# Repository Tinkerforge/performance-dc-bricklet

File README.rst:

Performance DC Bricklet
=======================

This repository contains the firmware source code and the hardware design
files. The documentation generator configs can be found at
https://github.com/Tinkerforge/generators

Repository Content
------------------

software/:
 * examples/: Examples for all supported languages
 * build/: Compiled files
 * src/: Source code of firmware
 * Makefile: Makefile to build project

hardware/:
 * Contains KiCad project files and additionally schematics as PDF

datasheets/:
 * Contains datasheets for sensors and complex ICs that are used

Hardware
--------

The hardware is designed with the open source EDA Suite KiCad
(http://www.kicad.org). Before you are able to open the files,
you have to install the Tinkerforge kicad-libraries
(https://github.com/Tinkerforge/kicad-libraries). You can either clone
them directly in hardware/ or clone them in a separate folder and
symlink them into hardware/
(ln -s kicad_path/kicad-libraries project_path/hardware). After that you
can open the .pro file in hardware/ with KiCad and from there view and
modify the schematics and the PCB layout.

Software
--------

If you want to do your own Brick/Bricklet firmware development we highly
recommend that you use our build environment setup script and read the
tutorial (https://www.tinkerforge.com/en/doc/Tutorials/Tutorial_Build_Environment/Tutorial.html).

To compile the C code we recommend you to install the newest GNU Arm Embedded
Toolchain (https://launchpad.net/gcc-arm-embedded/+download).
You also need to install bricklib2 (https://github.com/Tinkerforge/bricklib2).

You can either clone it directly in software/src/ or clone it in a
separate folder and symlink it into software/src/
(ln -s bricklib_path/bricklib2 project_path/software/src/). Finally make sure to
have CMake installed (http://www.cmake.org/cmake/resources/software.html).

After that you can build the firmware by invoking make in software/.
The firmware (.zbin) can then be found in software/build/ and uploaded
with brickv (click button "Flashing" on start screen).

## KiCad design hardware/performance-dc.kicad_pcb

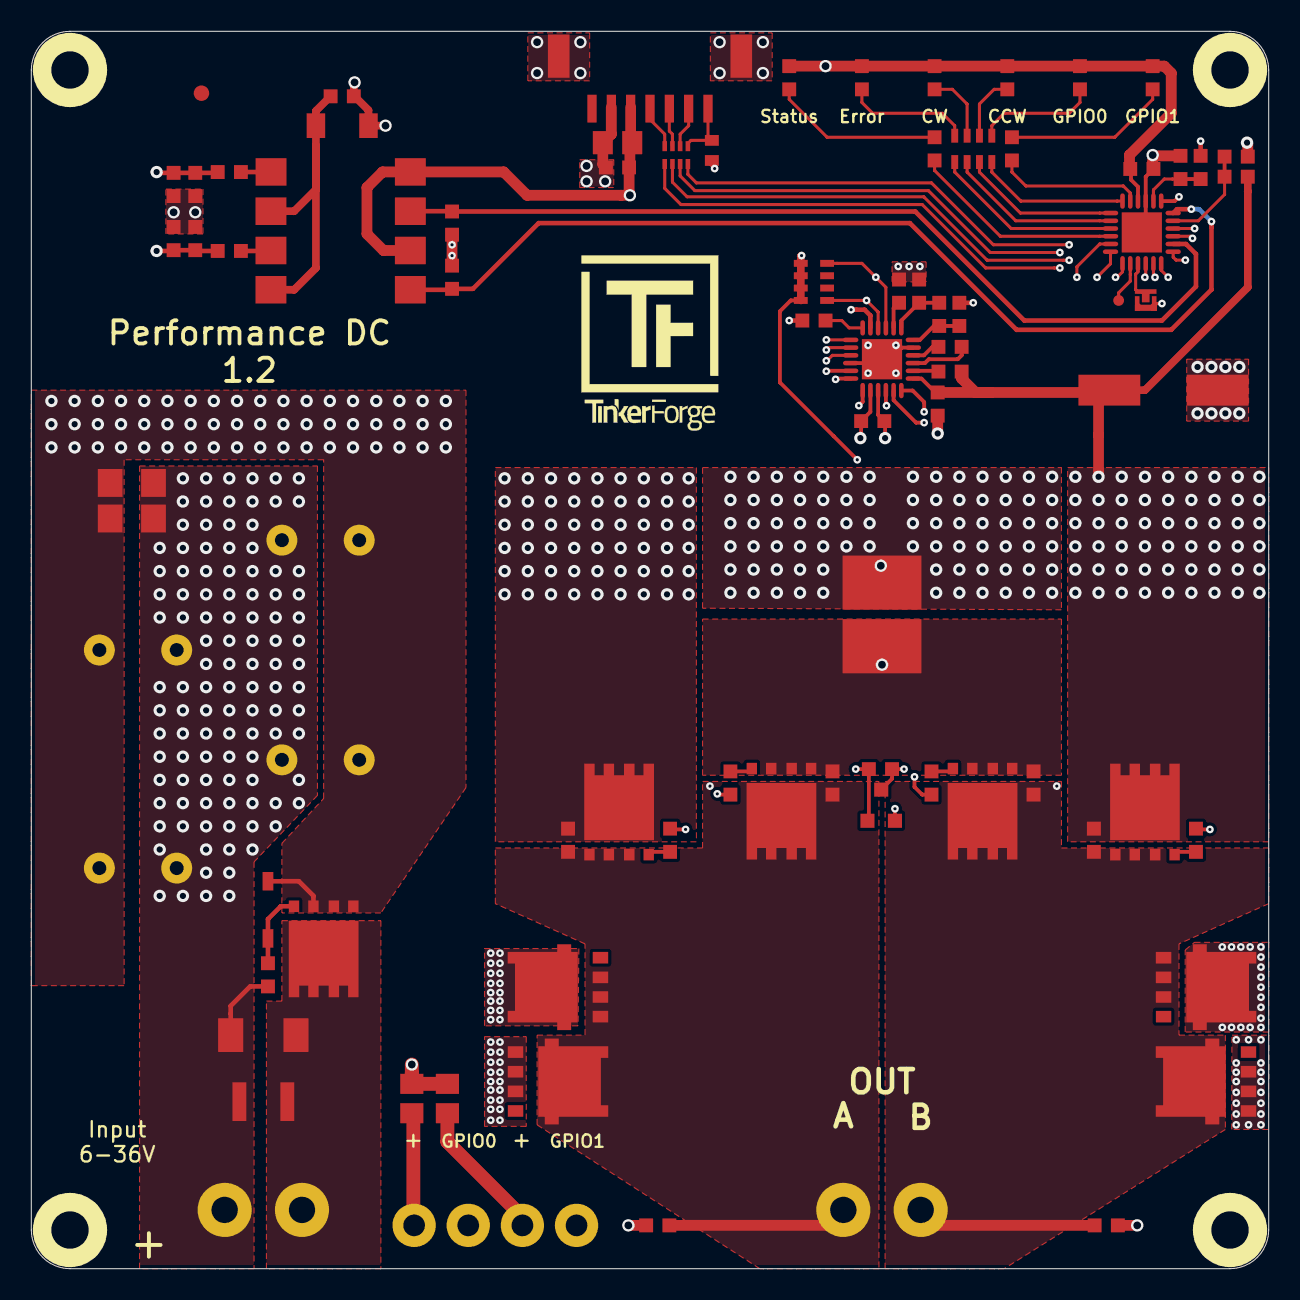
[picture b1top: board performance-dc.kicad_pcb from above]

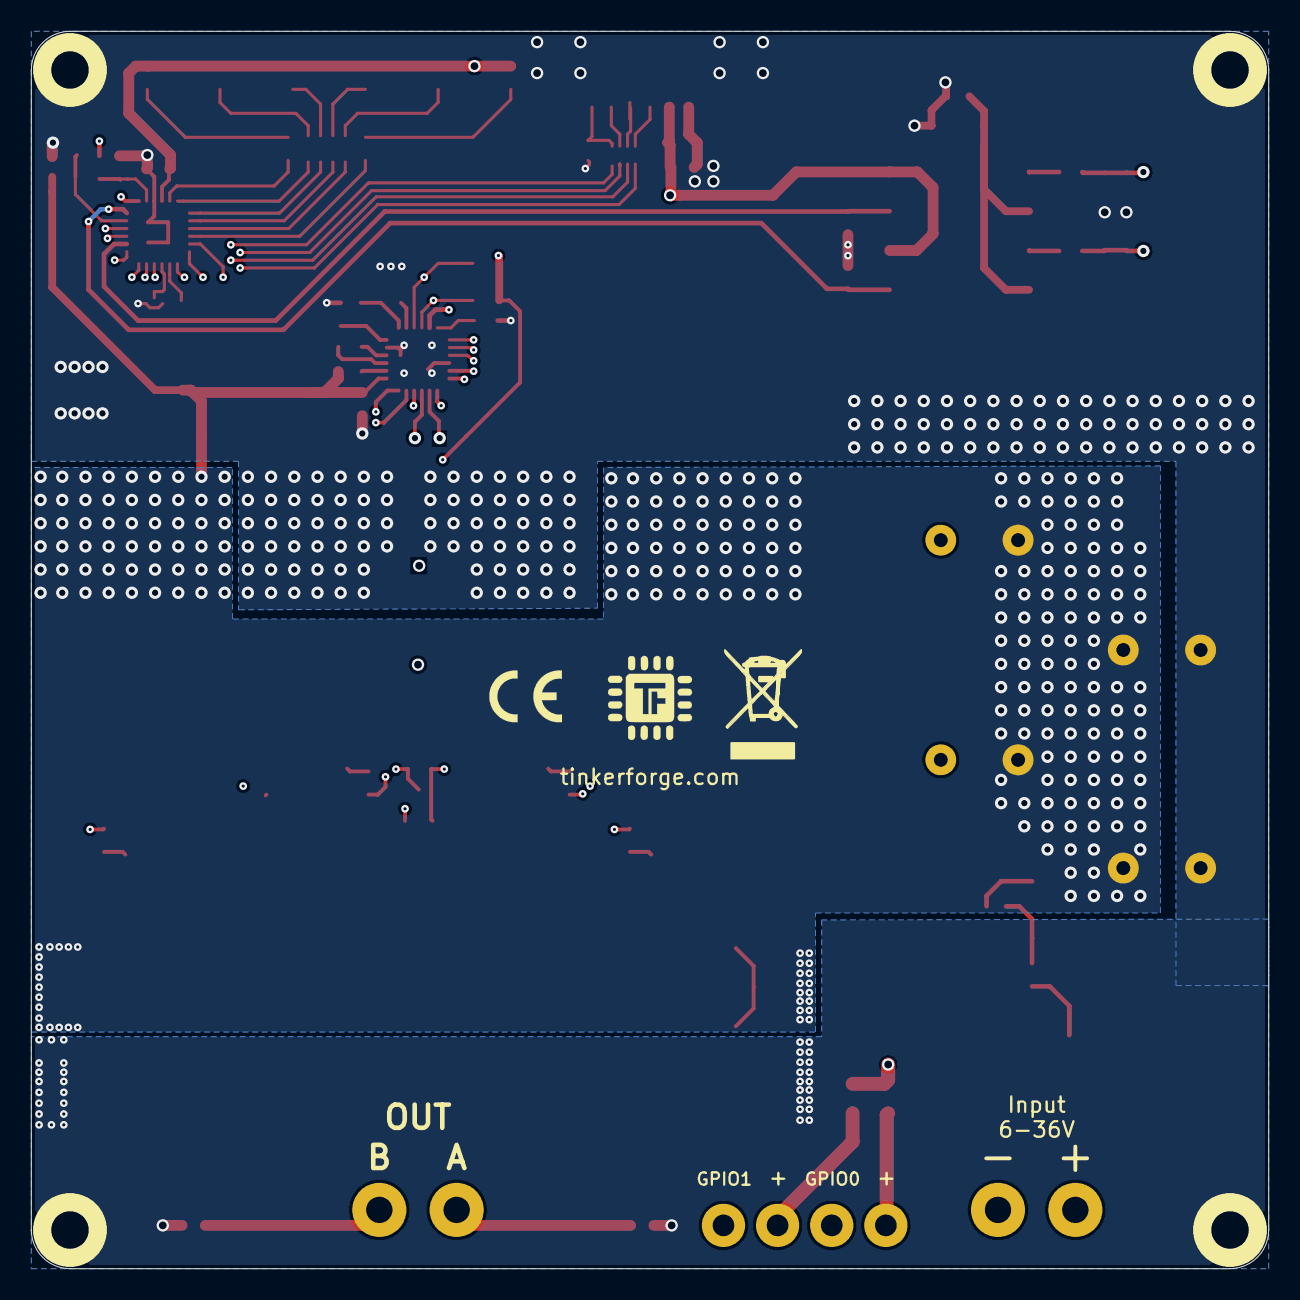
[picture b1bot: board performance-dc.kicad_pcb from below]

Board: 4 copper layers, 80.0 x 80.0 mm, 89 parts (2 on the bottom side), 63 nets.

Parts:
C1: 220pF; C0402E
C2: 10uF; C0805E
C3: 1uF; C0603F
C4, C27: 100nF; C0603F
C5, C6, C7: 1uF/16V; C0603F
C8, C9, C10, C11, C12: 100nF/100V; C0603F
C13: 10uF/100V; ELKO_83
C14: 1nF; C0603F
C15, C18: 1uF/100V; C1206E
C16, C17, C20, C21: DNP; C0603F
C19, C22, C25, C26: 220uF/100V/UVY2A221MHD1TO; ELKO_RAD_12
C23, C24: 1nF/100V; C0603F
D1, D8, D9, D10, D11: BLUE; D0603F
D2: Z12V; SOD-123
D3, D4, D5, D7: NTS12120EMFST1G; DFN5_5x6
D6: Z3,3V; MiniMelf
D12: RED; D0603F
D13: SMBJ36CA; SMB
Fiducial_Mark: VAL**; Fiducial_Mark
P1: CON-SENSOR2; CON-SENSOR2_180
P2: DEBUG; DEBUG_PAD
P3: BOOT; SolderJumper
P4: OUT; OQ_2P_5mm_Vertical
P5: GPIO; OQ_4P_Vertical
P6: IN; OQ_2P_5mm_Vertical_Black
Q1, Q2, Q3, Q4, Q5: CSD19533Q5A; SON_5x6mm
R1, R3, R10, R11, R12, R13: 1k; R0603F
R2: 7,5k; R0603F
R4, R6: 10k; R0603F
R5, R25: 100k; R0603F
R9: 200k; R0603F
R14, R15: 4,7k; R0603F
R16, R17: 2,2k; R0805E
R18, R20, R21, R22, R23: 0; R0603F
R19: DNP; R0603F
R24: 0,01/WSHM2818R0100FEA; R2818
R26: B72530T6250K062; 1210
RP1: 82; 4X0402
RP2: 1k; 4X0603
RP5: 1k; 0603X4
U1: XMC1302; QFN24-4x4mm-0.5mm
U2, U3, U4, U5: DRILL; DRILL_NP
U6: DRV8701P; QFN24-4x4mm-0.5mm
U7: LTV-827; DIP_8_SMD
U8: TMP235; SOT23-3
VAL: WEEE_7mm
VAL#2: CE_5mm

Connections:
+3.3VP: C2.1, C3.1, C4.1, C27.1, D1.1, D8.1, D9.1, D10.1, D11.1, D12.1, P1.3, RP2.1, RP2.2, RP2.3, RP2.4, U1.10, U7.6, U7.8, U8.1
AVDD: C6.1, R18.1, U6.7
GND: C1.2, C2.2, C3.2, C4.2, C5.2, C6.2, C9.2, C10.2, C11.2, C12.2, C13.2, C14.2, C15.2, C18.2, C19.2, C22.2, C23.2, C24.2, C25.2, C26.2, C27.2, D2.1, D4.1, D6.1, D7.1, P1.2, P1.EP, P3.1, Q5.S, R4.1, R6.2, R9.2, R10.1, R11.1, R14.2, R15.2, R19.2, R24.2, U1.9, U1.EXP, U6.5, U6.16, U6.20, U6.EXP, U8.3
GPIO0: R10.2, U1.2, U7.7
GPIO1: R11.2, U1.6, U7.5
IN1: U1.19, U6.15
IN2: U1.18, U6.14
unnamed: C1.1, P1.7, RP1.1
unnamed: C5.1, U6.8
unnamed: C7.2, U6.2
unnamed: C8.1, U6.3
unnamed: C8.2, U6.4
unnamed: C9.1, D6.2, U7.2, U7.4
unnamed: C11.1, P5.2, R12.1, R14.1
unnamed: C12.1, P5.4, R13.1, R15.1
unnamed: C14.1, C17.2, C21.2, Q2.S, Q4.S, R24.1, U6.21
unnamed: C16.2, C17.1, C23.1, D3.1, D4.2, P4.2, Q1.S, Q2.D, U6.23
unnamed: C20.2, C21.1, C24.1, D5.1, D7.2, P4.1, Q3.S, Q4.D, U6.18
unnamed: D1.2, R1.2
unnamed: D2.2, Q5.G, R25.2
unnamed: D8.2, R3.2
unnamed: D9.2, RP5.1
unnamed: D10.2, RP5.2
unnamed: D11.2, RP5.3
unnamed: D12.2, RP5.4
unnamed: D13.2, P6.2, Q5.D, R26.2
unnamed: P1.4, RP1.4
unnamed: P1.5, RP1.3
unnamed: P1.6, RP1.2
unnamed: P2.1, U1.20
unnamed: P3.2, U1.21
unnamed: P5.1, R16.1
unnamed: P5.3, R17.1
unnamed: Q1.G, R22.1
unnamed: Q2.G, R23.1
unnamed: Q3.G, R20.1
unnamed: Q4.G, R21.1
unnamed: R1.1, U1.16
unnamed: R2.1, R4.2, U1.8
unnamed: R3.1, U1.11
unnamed: R9.1, U6.12
unnamed: R12.2, U7.1
unnamed: R13.2, U7.3
unnamed: R18.2, R19.1, U6.6
unnamed: R20.2, U6.17
unnamed: R21.2, U6.19
unnamed: R22.2, U6.24
unnamed: R23.2, U6.22
unnamed: RP5.5, U1.15
unnamed: RP5.6, U1.14
unnamed: RP5.7, U1.13
unnamed: RP5.8, U1.12
S-CLK: RP1.6, U1.23
S-CS: RP1.5, U1.22
S-MISO: RP1.8, U1.1
S-MOSI: RP1.7, U1.24
SNSOUT: RP2.8, U1.4, U6.10
SO: R2.2, U6.11
TEMP: U1.7, U8.2
VIN: R5.2, R6.1, U1.5
V_GPIO: C7.1, C10.1, C13.1, C15.1, C16.1, C18.1, C19.1, C20.1, C22.1, C25.1, C26.1, D3.2, D5.2, D13.1, P6.1, Q1.D, Q3.D, R5.1, R16.2, R17.2, R25.1, R26.1, U6.1
nFAULT: RP2.5, U1.3, U6.9
nSLEEP: U1.17, U6.13

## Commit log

2019-09-03 initial push
2019-09-03 corrected readme
2019-09-03 first protoype schematic
2019-09-12 Add sym-lib-table
2020-01-15 added schematics
2020-01-16 first pcb layout idea
2020-02-05 ready for prototype
2020-02-06 drc check and ordered prototype
2020-04-09 new DRV8701 design
2020-04-09 changes in schematic
2020-04-14 new design
2020-04-21 safety save
2020-04-24 added input voltage to silkscreen and drc
2020-05-08 changed resistor footprint
2020-06-05 Add initial firmware for DC Bricklet 2.0
    (currently still in development)
2020-06-05 Add GPIO config per channel and action support
2020-06-09 Fix device name
2020-07-08 added temperature sensor, and changed protection diodes
2020-07-23 new hardware version
2020-08-06 changed mosfet pin 1 on fab layer
2020-08-06 added logos to back silkscreen
2020-09-08 changed input voltage silkscreen
2020-09-08 Add support for temperature sensor
2020-09-09 Version 2.2 : changed name, changed silkscreen, added resistor value for Vref
2020-09-09 changed name and silkscreen ro Version 1.2
2020-10-14 updated all OQ connectors with new F.Fab layer
2020-10-28 specify processor
2020-11-06 specify drv8701p
2020-11-11 Rename to "Performance DC Bricklet"
2020-11-11 Adjust defines to new name
2020-11-11 Add thermal studown and callback API stubs
2020-11-19 Add velocity-reached and thermal-shutdown support
2020-11-19 Remove unused velocity_current variable
    We instead use the high resolution version everywhere
2020-11-19 Add callback and thermal shutdown tests
2020-11-20 Fix typo
2020-11-20 Add nfault pin fault detection
2021-01-12 Add thermal shutdown as error LED trigger
2021-01-14 Add examples
2021-01-15 rust: Fix compiler warning
2021-01-18 Make sure heartbeat-tick is called if configured
2021-02-17 Add GPIO test
2021-02-17 Set default LED config to active high
2021-02-17 Add API for GPIO State callback
2021-02-17 Add ref for 2.0.1
2021-03-08 add schematic
2021-05-05 python: Fix passing pdc object to callback
2021-05-27 readme: Remove in-development marker
2021-05-28 fix 3d path
2021-10-25 Update KiCad link
    https://www.kicad.org/blog/2021/10/Avoid-links-to-former-kicad-domain/
2022-04-19 examples: uc: Rename TF_HalContext to TF_HAL.
2022-04-26 uc: Adapt to bindings changes
2022-07-06 Add license files.
2022-07-19 add partial 3d files
2025-10-04 Fix compatibility with new Docker build image (GCC 14.2.1)

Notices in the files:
hardware/performance-dc.kicad_pcb:
Licensed under CERN OHL v.1.1
Copyright (©) 2020, T.Schneidermann
Copyright Tinkerforge GmbH 2020.
This documentation describes Open Hardware and is licensed under the
CERN OHL v. 1.1.
